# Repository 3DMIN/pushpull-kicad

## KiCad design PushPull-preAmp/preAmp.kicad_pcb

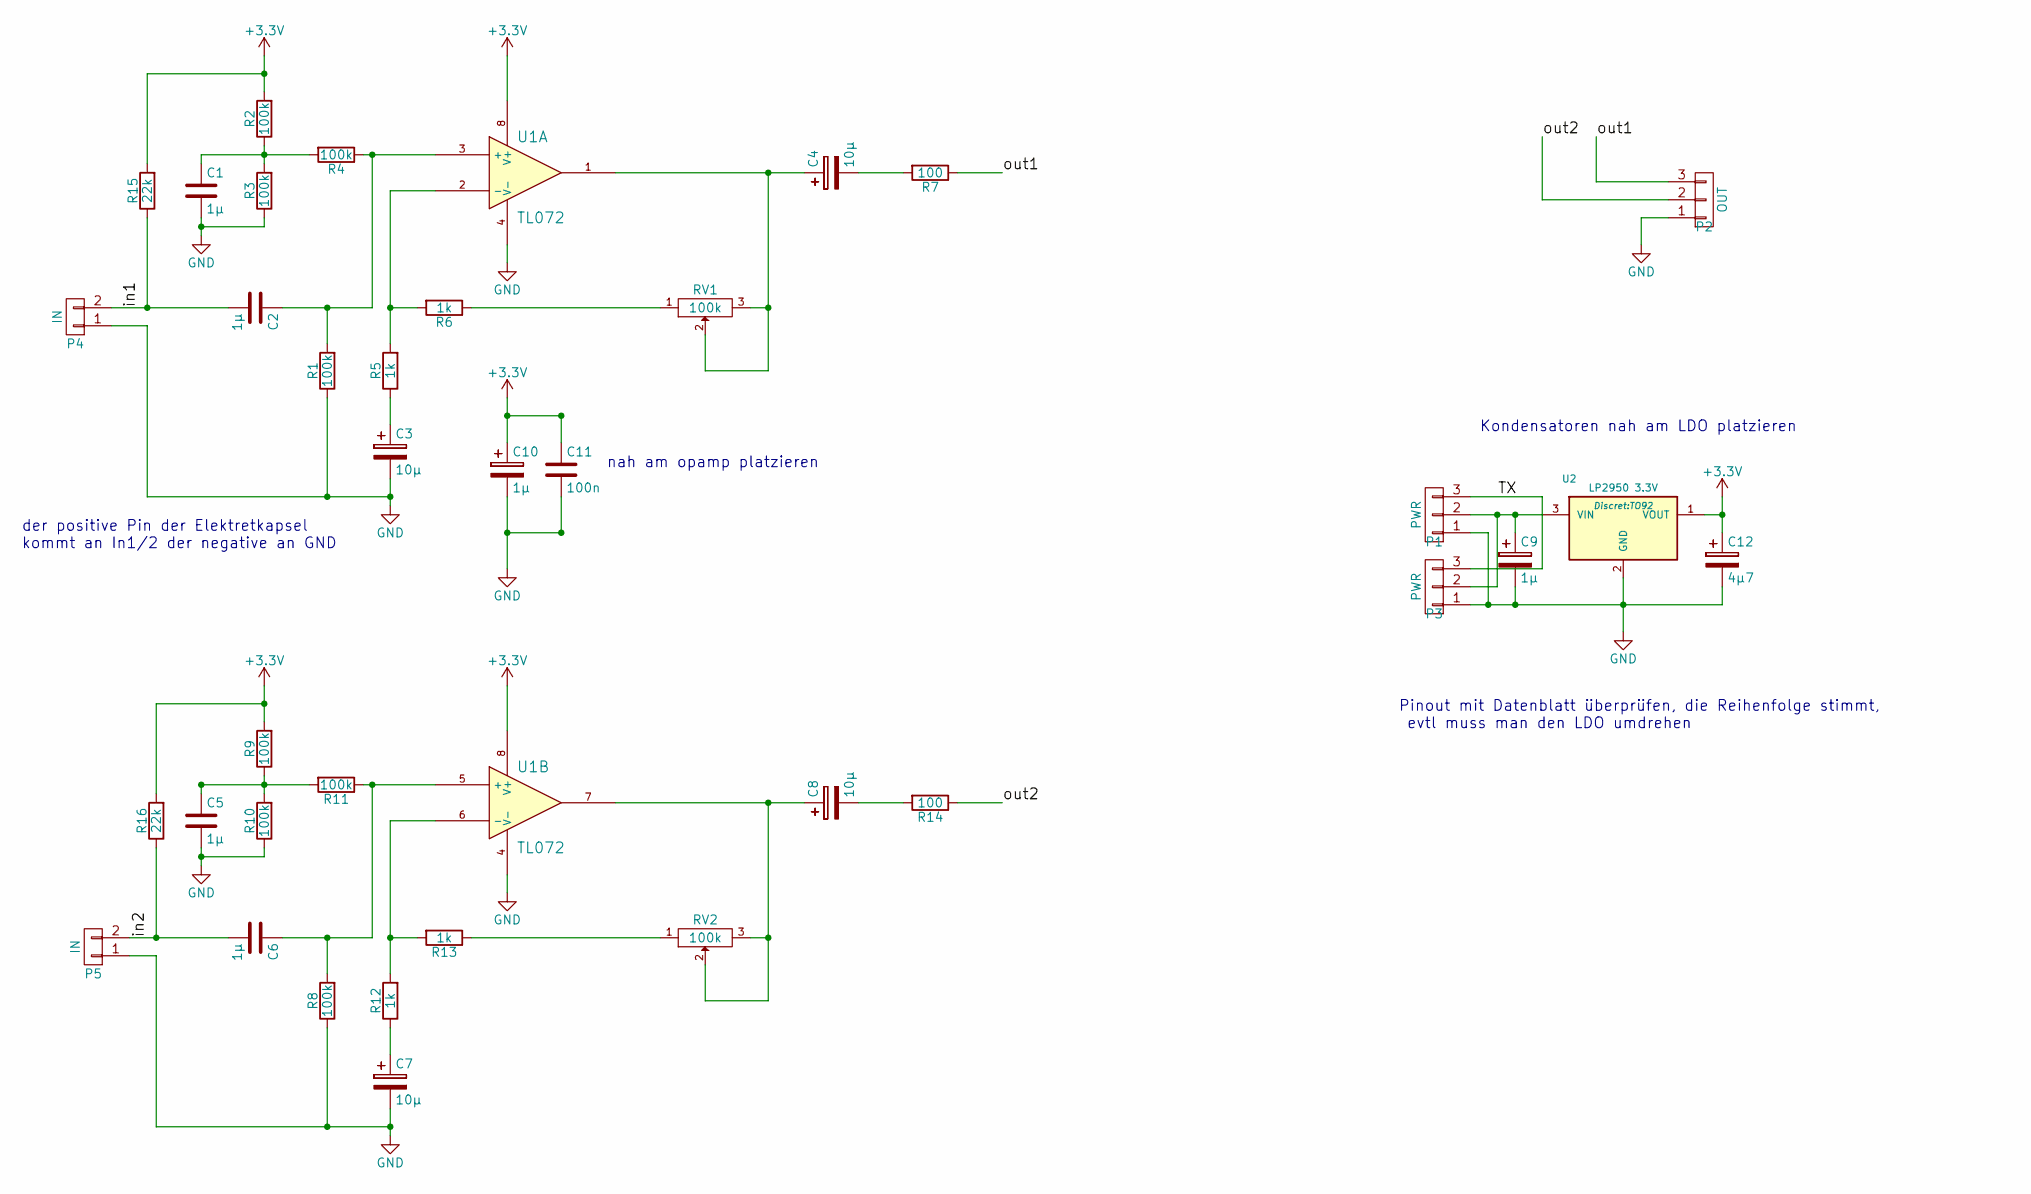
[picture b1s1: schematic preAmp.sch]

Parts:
C1, C5, C9, C10: 1µ; Elko_vert_11.2x6.3mm_RM2.5
C2, C6: 1µ; C_Rect_L7_W4.5_P5
C3, C4, C7, C8: 10µ; Elko_vert_11.2x6.3mm_RM2.5
C11: 100n; C_Rect_L4_W2.5_P2.5
C12: 4µ7; Elko_vert_11.2x6.3mm_RM2.5
P1, P3: PWR; Pin_Header_Straight_1x03
P2: OUT; Pin_Header_Straight_1x03
P4, P5: IN; Pin_Header_Straight_1x02
R1, R2, R3, R4, R8, R9, R10, R11: 100k; Resistor_Horizontal_RM10mm
R5, R6, R12, R13: 1k; Resistor_Horizontal_RM10mm
R7, R14: 100; Resistor_Horizontal_RM10mm
R15, R16: 22k; Resistor_Horizontal_RM10mm
RV1, RV2: 100k; Trimmer_Dual
U1: TL072; DIP-8__300_ELL
U2: LP2950 3.3V; TO92

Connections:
+3V3: C10.1, C11.1, C12.1, R2.2, R9.2, R15.2, R16.2, U1.8 (V+), U2.1 (VOUT)
/TX: P1.3, P3.3
/in1: C2.2, P4.2, R15.1
/in2: C6.2, P5.2, R16.1
/out1: P2.3, R7.1
/out2: P2.2, R14.1
GND: C1.2, C3.2, C5.2, C7.2, C9.2, C10.2, C11.2, C12.2, P1.1, P2.1, P3.1, P4.1, P5.1, R1.1, R3.1, R8.1, R10.1, U1.4 (V-), U2.2 (GND)
unnamed: C1.1, R2.1, R3.2, R4.2
unnamed: C2.1, R1.2, R4.1, U1.3 (+)
unnamed: C3.1, R5.1
unnamed: C4.1, RV1.2, RV1.3, U1.1
unnamed: C4.2, R7.2
unnamed: C5.1, R9.1, R10.2, R11.2
unnamed: C6.1, R8.2, R11.1, U1.5 (+)
unnamed: C7.1, R12.1
unnamed: C8.1, RV2.2, RV2.3, U1.7
unnamed: C8.2, R14.2
unnamed: C9.1, P1.2, P3.2, U2.3 (VIN)
unnamed: R5.2, R6.2, U1.2 (-)
unnamed: R6.1, RV1.1
unnamed: R12.2, R13.2, U1.6 (-)
unnamed: R13.1, RV2.1

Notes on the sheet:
nah am opamp platzieren
Kondensatoren nah am LDO platzieren
der positive Pin der Elektretkapsel kommt an In1/2 der negative an GND
Pinout mit Datenblatt überprüfen, die Reihenfolge stimmt, evtl muss man den LDO umdrehen

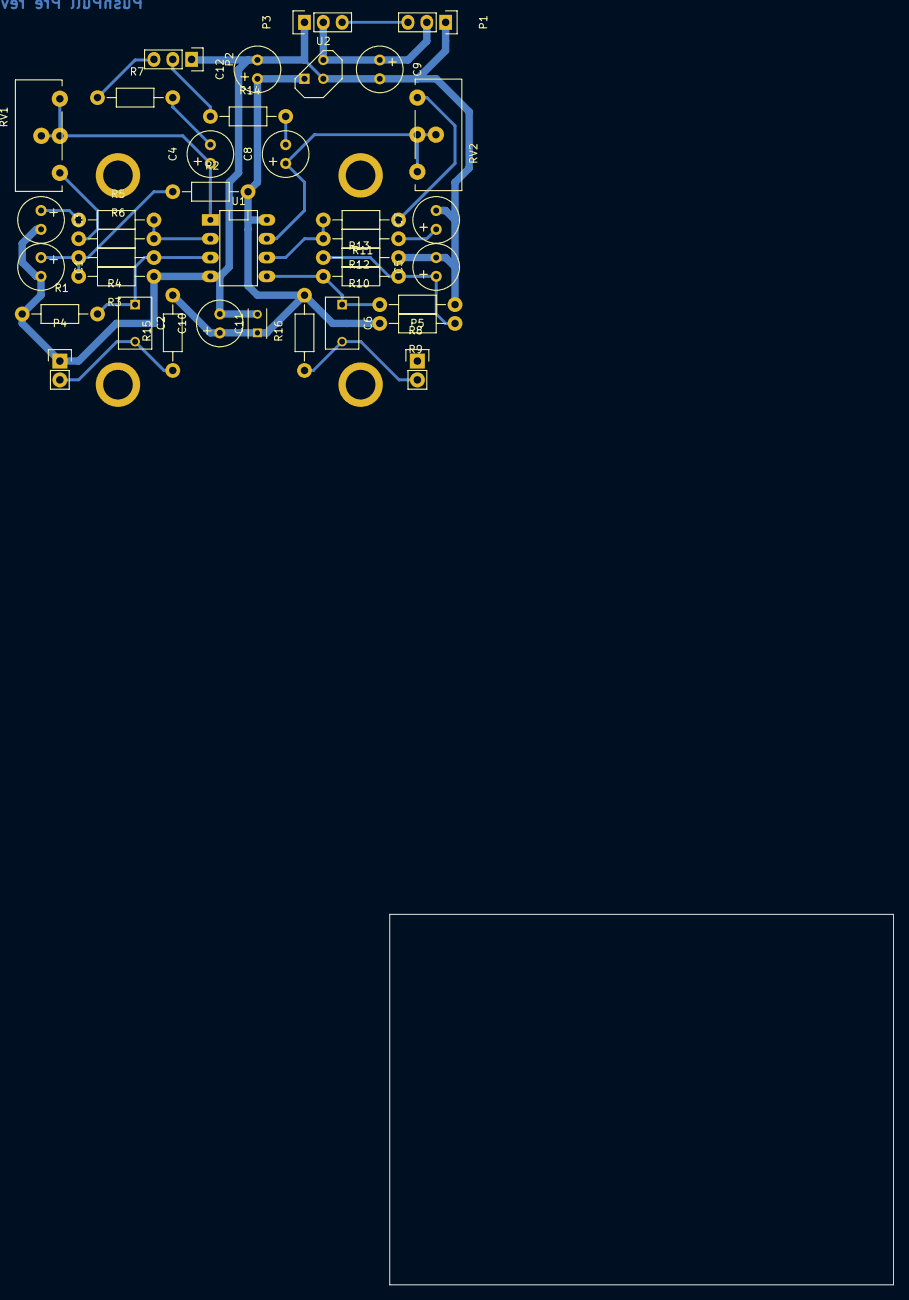
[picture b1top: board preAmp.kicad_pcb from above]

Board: 2 copper layers, 68.0 x 50.0 mm, 37 parts (0 on the bottom side), 22 nets.

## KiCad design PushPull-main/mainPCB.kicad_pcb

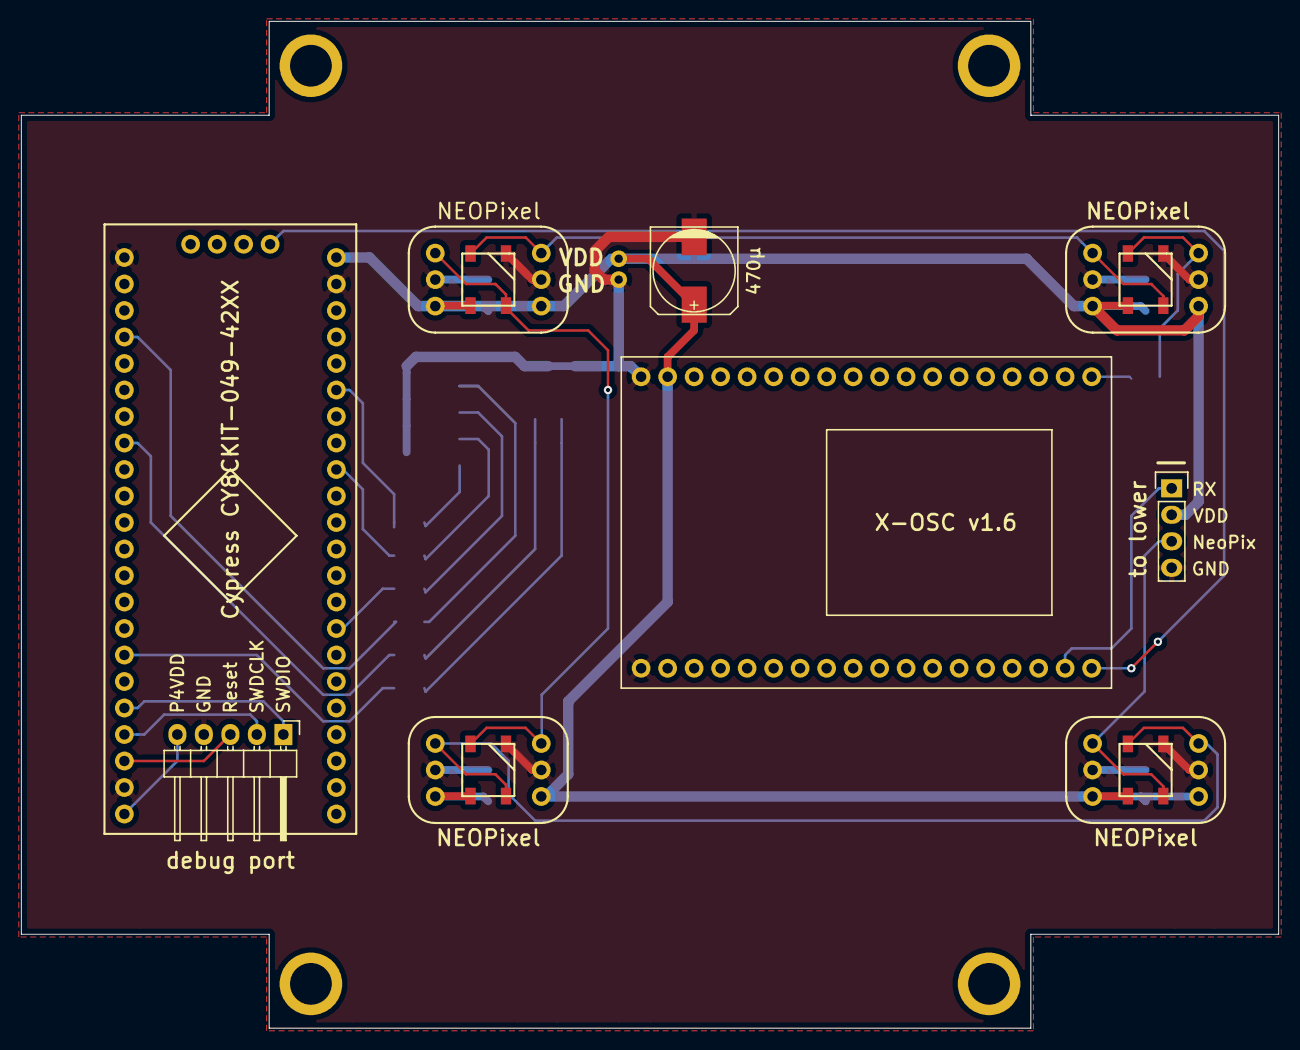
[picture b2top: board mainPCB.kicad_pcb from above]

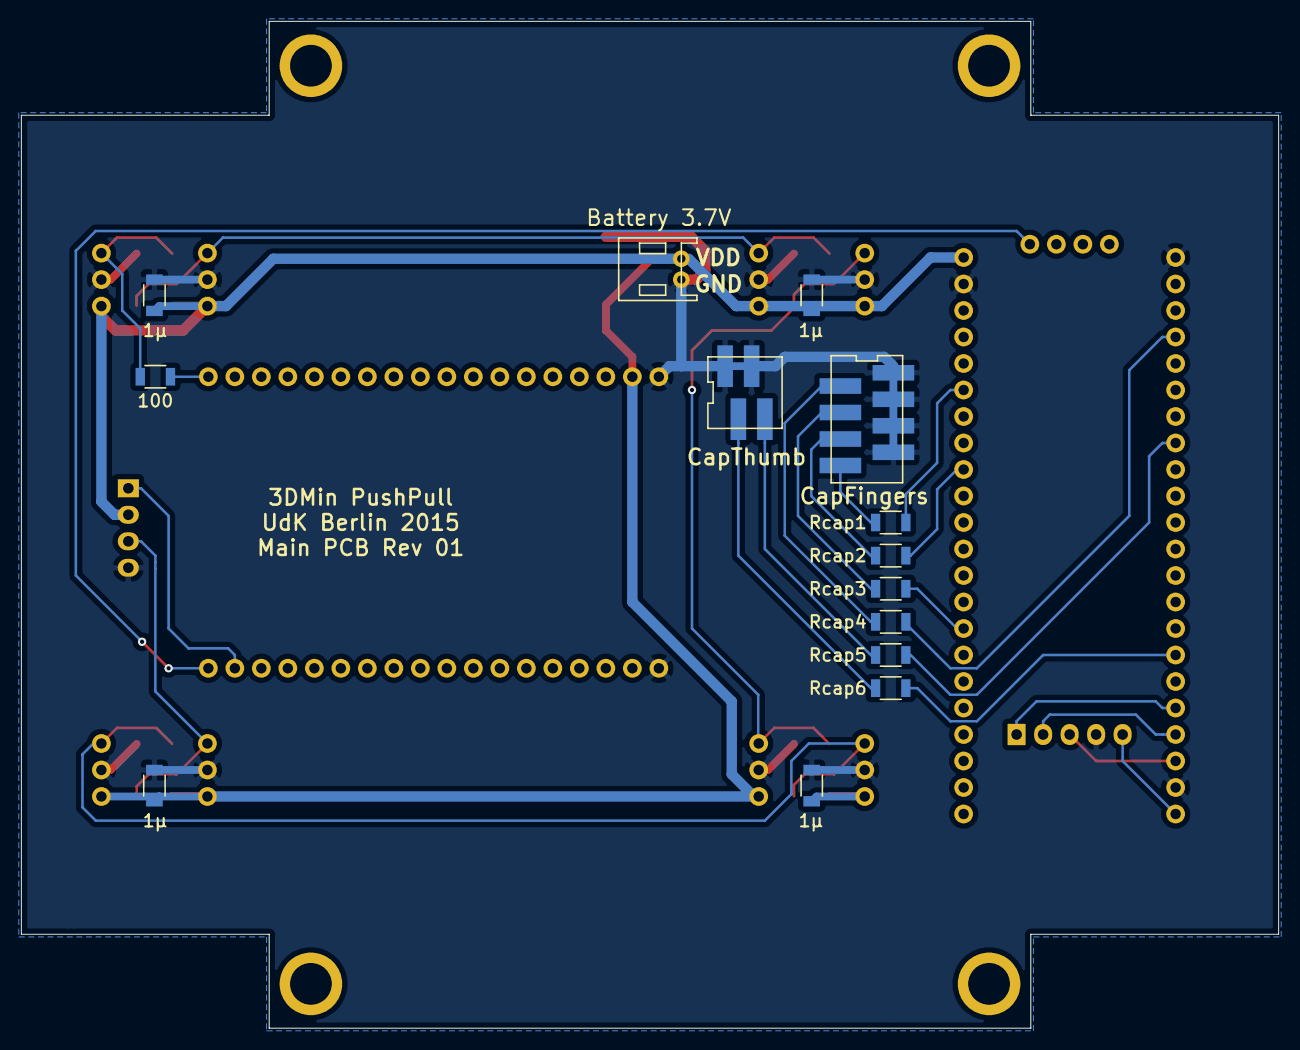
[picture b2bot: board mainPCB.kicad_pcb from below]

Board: 2 copper layers, 120.5 x 96.5 mm, 23 parts (14 on the bottom side), 26 nets.

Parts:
C1, C2, C3, C4: 1µ; C_1206
C5: 470µ; c_elec_8x10
P1: Battery 3.7V; JST_PH_Series_S2B-PH-KL-2pole_angled
P2: CapFingers; 8_PIN_MM_conn
P3: to lower; Pin_Header_Straight_1x04
P4: debug port; Pin_Header_Angled_1x05
P5: CapThumb; 4_PIN_MM_conn
R1: Rcap1; R_1206
R2: Rcap2; R_1206
R3: Rcap3; R_1206
R4: Rcap4; R_1206
R5: Rcap5; R_1206
R6: Rcap6; R_1206
R7: 100; R_1206
U1, U2, U3, U4: NEOPixel; NeoPixel_WS2812B
U5: X-OSC v1.6; XOsc
U6: Cypress CY8CKIT-049-42XX; Psoc

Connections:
GND: C1.2, C2.2, C3.2, C4.2, C5.2, P1.1, P2.2, P2.4, P2.6, P2.8, P3.4, P4.4, P5.2, P5.4, U1.2, U1.5, U2.2, U2.5, U3.2, U3.5, U4.2, U4.5, U5.1, U5.36, U6.1, U6.21, U6.43
unnamed: P2.1, R1.2
unnamed: P2.3, R2.2
unnamed: P2.5, R3.2
unnamed: P2.7, R4.2
unnamed: P3.1, U5.17
unnamed: P3.3, U4.4
unnamed: P4.1, U6.18
unnamed: P4.2, U6.19
unnamed: P4.3, U6.20
unnamed: P4.5, U6.22
unnamed: P5.1, R5.2
unnamed: P5.3, R6.2
unnamed: R1.1, U6.39
unnamed: R2.1, U6.36
unnamed: R3.1, U6.30
unnamed: R4.1, U6.4
unnamed: R5.1, U6.8
unnamed: R6.1, U6.16
unnamed: R7.1, U1.3
unnamed: R7.2, U5.19
unnamed: U1.4, U2.3
unnamed: U2.4, U3.3
unnamed: U3.4, U4.3
unnamed: U5.18, U6.45
VDD: C1.1, C2.1, C3.1, C4.1, C5.1, P1.2, P3.2, U1.1, U1.6, U2.1, U2.6, U3.1, U3.6, U4.1, U4.6, U5.35, U6.44

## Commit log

2015-05-12 initial
2015-06-01 added preAmp outline
2015-06-02 production pcb kicad files and gerbers
2015-06-02 updated footprints
2015-06-02 electret capsule bias, small fixes
2015-06-03 preamp layout single sided
2015-06-04 preamp layout drills
2015-08-24 added fingergutter SE
2015-08-26 pushpull left hand version cap sense
2016-10-26 updates.
